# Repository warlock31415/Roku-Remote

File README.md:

# Roku Remote

## Introduction
My roomate keeps loosing the remote to the TV. So I made a spare remote to work with our TV and simulates the same behaviour as the original remote. The remote can also work via micro USB as well as a Lithium polymer battery. This project was my first forray into ARM microcontrollers and ST's Hardware Abstraction Layer (HAL).  

## Recording button codes
The Roku remote work on a IR signal and the data is modulated on the 37 kHz signal. The NEC protocol decription can be found [here](https://techdocs.altium.com/display/FPGA/NEC+Infrared+Transmission+Protocol) . A Analog Discovery along with the TSOP382 (IR receiver) was used to record the signal. The receiver demodulates the signal internally and only ouputs the data bits. Each button was pressed and the corresponding code was recorded. It was noted that each button had 2 codes associated with it. The first one was transmitted when the button was pressed and the second was transmitted when the button was held down. Only the last 4 bytes of the codes are shown here as the first 4 bytes are always the same (0x57E3).

The recorded button codes are as follows:
| Button | Code in HEX |  Last 4 bytes of the held down code|
|--------|-------------| ----------|
| Power  | 0x57E3E817 | 0x57E3E916 | 
| Back   | 0x57E36699 | 0x57E36798 |
| Home   | 0xCO3F | 0xC13E |
| ↑      | 0x9867 | 0x9966 |
| →      | 0xB44B | 0xB54A |
| ↓      | 0xCC33 | 0xCD32 |
| ←      | 0x7887 | 0x7986 |
| OK     | 0x54AB | 0x55AA |
| V+     | 0xF00F | 0xF10E |
| V-     | 0x08F7 | 0x09F6 |
| Mute   | 0x04FB | 0x05FA |

## The code
ST's Nucleo-F401RE(497-14360-ND) was used to build the remote on a breadboard. Although, a STM32L052K8T was actually used in the final prototype due to its lower power consumption as compared to the STM32F401RE.

The HAL does not have a microsecond delay so a timer was used. The following code shows how this works:
```
void delay_us(uint16_t time)
{
	TIM6->ARR = time; 	 	// Load time into Auto Reload Register
	TIM6->CR1 |= (1<<0); 	// start timer

	while(TIM6->CR1 & 1);	// Wait for timer to elapse
}
```
ST's Cube IDE makes it very easy to set up and use timers graphically. To generate the carrier another 16-bit advanced timer was used in PWM mode. The STM32F401RE has 16-bit prescale register which allows just about any frequency. This, combined with the Auto-Preload Register, one can generate just about any frequency signal with any duty cycle. So a 37kHz carrier with a 30% duty cycle, for efficiency, was generated. This Prescale and AR registers are especially more advatageous to an ATMEGA328P which only has a couple of prescalers to choose from and the "auto reload register" is the only way to control frequency. And hence duty cycle cannot be controlled in the same way.

Each button code consists of 3 sections. The start code, specific button code and the end code. This can be seen in Table 1.
## PCB
The PCB was made in Eagle and manufactured by JLCPCB. All components were hand soldered. Including, the STM32L052K8T. The blue silk screen on the PCBs look pretty good. 

## Shortcomings
- The SMD IR transmitter that was spec'd for the project didn't seem to work properly. So a THT transmitter, was was used to test the breadboard prototype, was soldered in its place. Some wire bodging was needed to accomplish this.
- The battery protection circuitry was not correctly wired up (Some kind of issue with Battery GND vs system GND).

## TO DO
- Redo board to eliminate wire bodges.
- Make a case for the board.

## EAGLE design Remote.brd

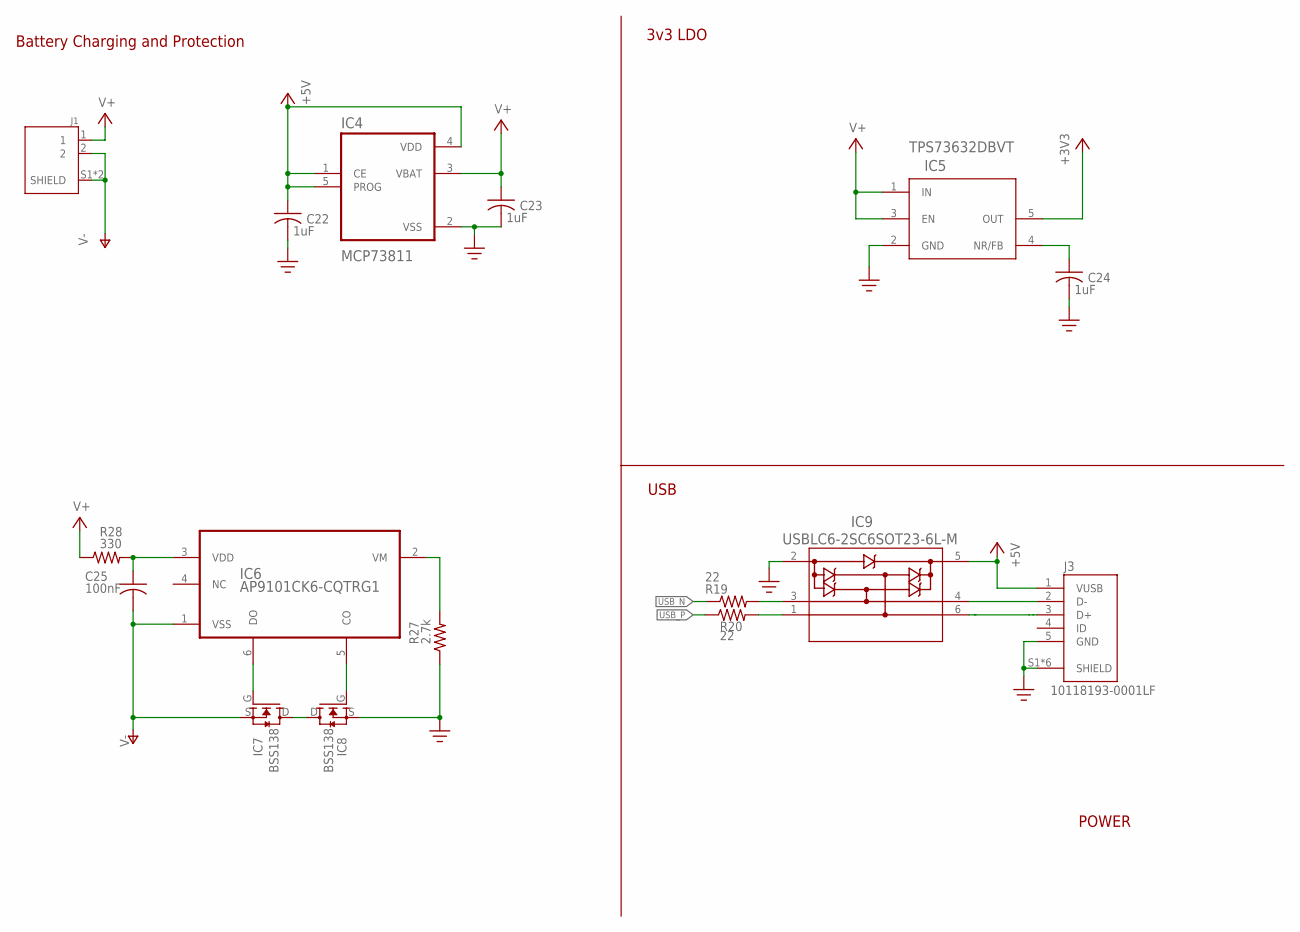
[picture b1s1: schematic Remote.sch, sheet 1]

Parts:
C22, C23, C24: 1uF; C0805K
C25: 100nF; C0805K
IC4: MCP73811; SOT95P280X145-5N
IC5: TPS73632DBVT; DBV5-M
IC6: AP9101CK6-CQTRG1; SOT95P280X140-6N
IC7, IC8: BSS138
IC9: USBLC6-2SC6SOT23-6L-M; SOT23-6L-M
J1: S2B-PH-SM4-TB(LF)(SN); JST_S2B-PH-SM4-TB(LF)(SN)
J3: 10118193-0001LF; FCI_10118193-0001LF
R19, R20: 22; R0805W
R27: 2.7k; R0805W
R28: 330; R0805W

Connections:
+3V3: IC5.5 (OUT); also elsewhere on the board
+5V: C22.1, IC4.1 (CE), IC4.4 (VDD), IC4.5 (PROG), IC9.5 (VBUS), J3.1 (VUSB); also elsewhere on the board
GND: C22.2, C23.2, C24.2, IC4.2 (VSS), IC5.2 (GND), IC8.S, IC9.2 (GND), J3.5 (GND), J3.S1 (SHIELD), J3.S2 (SHIELD), J3.S3 (SHIELD), J3.S4 (SHIELD), J3.S5 (SHIELD), J3.S6 (SHIELD), R27.1; also elsewhere on the board
unnamed: IC6.6 (DO), IC7.G
unnamed: IC6.5 (CO), IC8.G
unnamed: IC7.D, IC8.D
unnamed: C24.1, IC5.4 (NR/FB)
unnamed: IC6.2 (VM), R27.2
unnamed: C25.1, IC6.3 (VDD), R28.2
USB2_N: IC9.4 (I/O2), J3.2 (D-)
USB2_P: IC9.6 (I/O1), J3.3 (D+)
USB3_N: IC9.3 (I/O2_2), R19.2
USB3_P: IC9.1 (I/O1_2), R20.2
USB_N: R19.1; also elsewhere on the board
USB_P: R20.1; also elsewhere on the board
V+: C23.1, IC4.3 (VBAT), IC5.1 (IN), IC5.3 (EN), J1.1, R28.1; also elsewhere on the board
V-: C25.2, IC6.1 (VSS), IC7.S, J1.2, J1.S1 (SHIELD), J1.S2 (SHIELD)

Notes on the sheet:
Battery Charging and Protection
3v3 LDO
USB
POWER

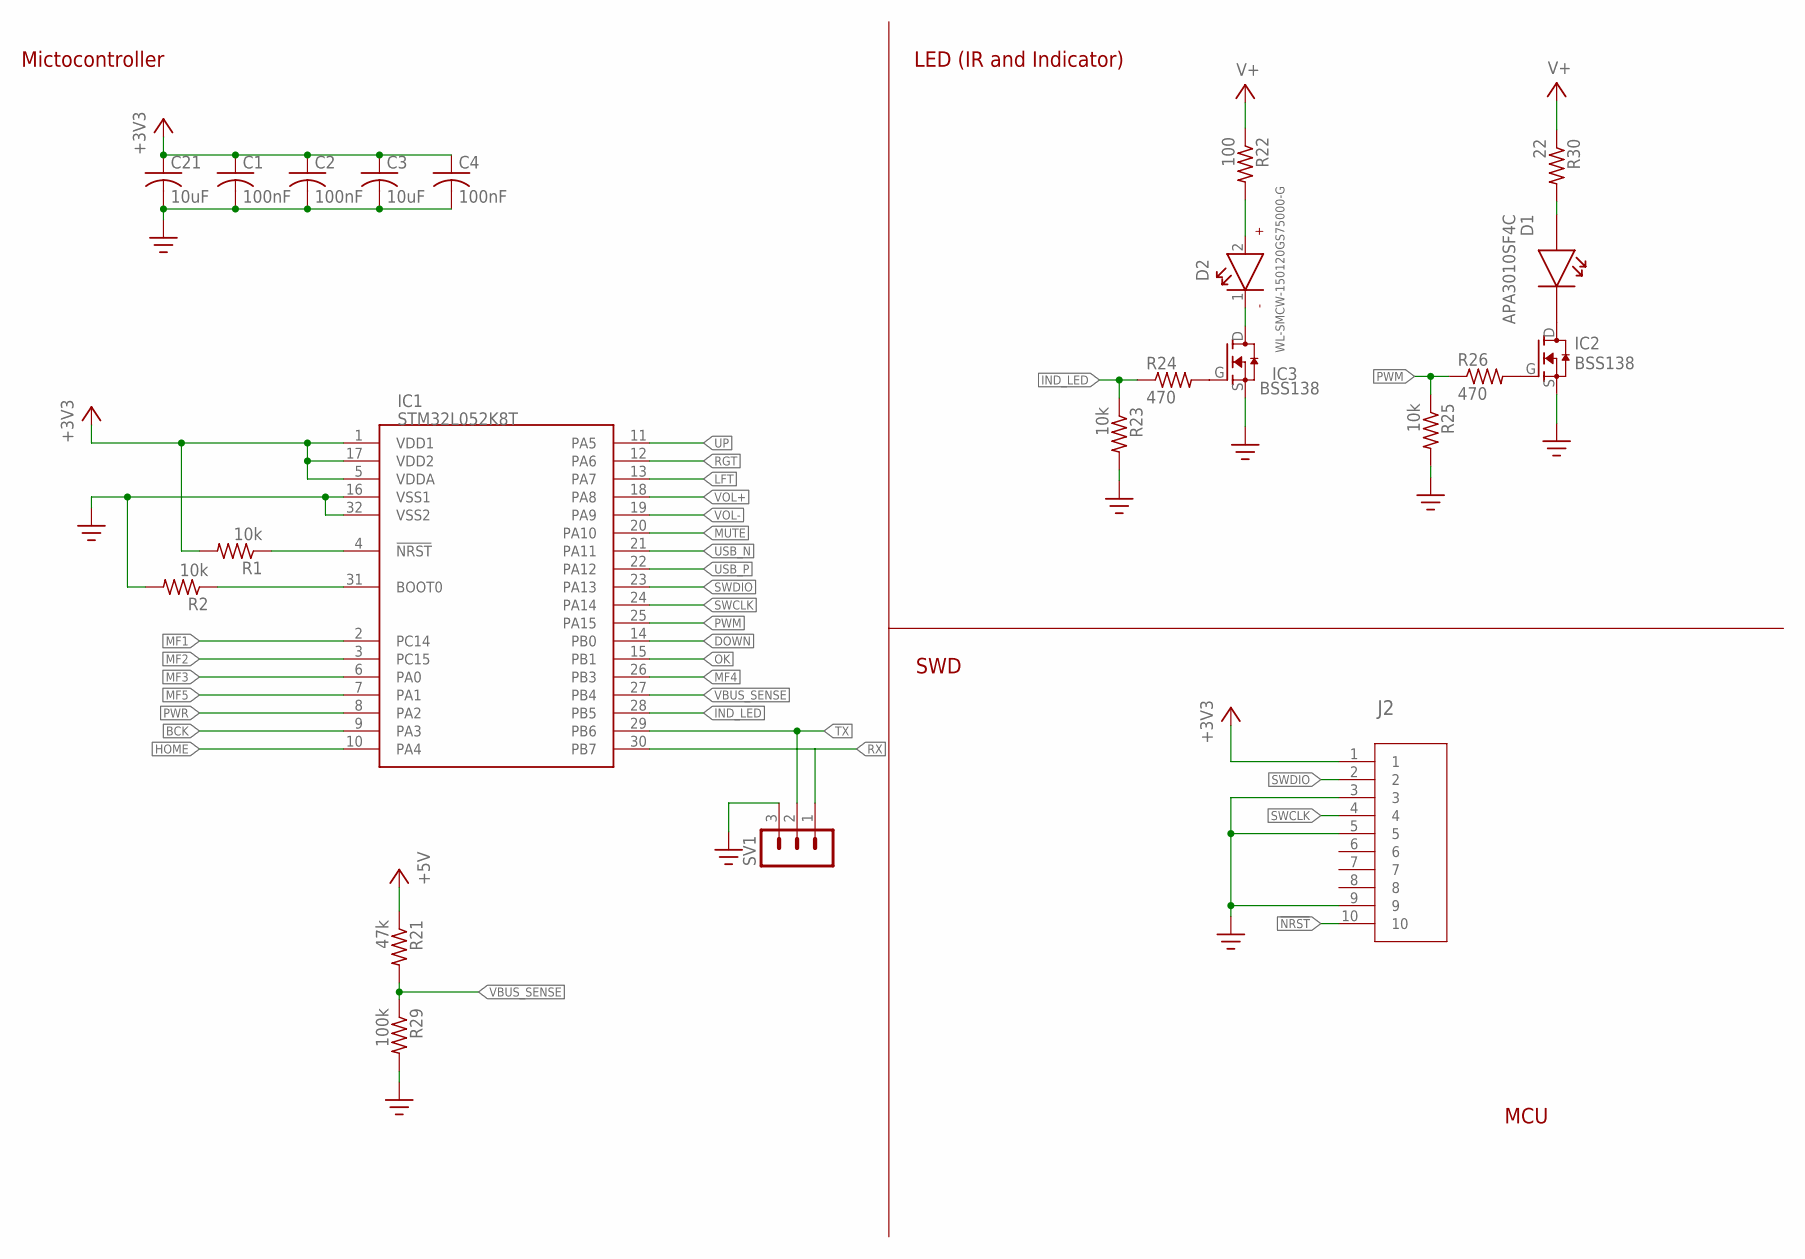
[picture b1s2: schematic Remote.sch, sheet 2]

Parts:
C1, C2, C4: 100nF; C0805K
C3, C21: 10uF; C0805K
D1: APA3010SF4C
D2: WL-SMCW-150120GS75000-G; WL-SMCW_1206
IC1: STM32L052K8T; QFP80P900X900X160-32N
IC2, IC3: BSS138
J2: 20021121-00010C4LF; CONN_00010C4LF_AMP
R1, R2, R23, R25: 10k; R0805W
R21: 47k; R0805W
R22: 100; R0805W
R24, R26: 470; R0805W
R29: 100k; R0805W
R30: 22; R0805W
SV1: MA03-1

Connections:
!NRST: IC1.4 (!NRST), J2.10, R1.1
+3V3: C1.1, C2.1, C3.1, C4.1, C21.1, IC1.1 (VDD1), IC1.5 (VDDA), IC1.17 (VDD2), J2.1, R1.2; also elsewhere on the board
+5V: R21.1; also elsewhere on the board
BCK: IC1.9 (PA3); also elsewhere on the board
DOWN: IC1.14 (PB0); also elsewhere on the board
GND: C1.2, C2.2, C3.2, C4.2, C21.2, IC1.16 (VSS1), IC1.32 (VSS2), IC2.S, IC3.S, J2.3, J2.5, J2.9, R2.2, R23.2, R25.2, R29.2, SV1.3; also elsewhere on the board
HOME: IC1.10 (PA4); also elsewhere on the board
IND_LED: IC1.28 (PB5), R23.1, R24.1
LFT: IC1.13 (PA7); also elsewhere on the board
MF1: IC1.2 (PC14); also elsewhere on the board
MF2: IC1.3 (PC15); also elsewhere on the board
MF3: IC1.6 (PA0); also elsewhere on the board
MF4: IC1.26 (PB3); also elsewhere on the board
MF5: IC1.7 (PA1); also elsewhere on the board
MUTE: IC1.20 (PA10); also elsewhere on the board
unnamed: D1.1, R30.2
unnamed: IC1.31 (BOOT0), R2.1
unnamed: D1.2, IC2.D
unnamed: D2.2 (+), R22.2
unnamed: D2.1 (-), IC3.D
unnamed: IC2.G, R26.2
unnamed: IC3.G, R24.2
OK: IC1.15 (PB1); also elsewhere on the board
PWM: IC1.25 (PA15), R25.1, R26.1
PWR: IC1.8 (PA2); also elsewhere on the board
RGT: IC1.12 (PA6); also elsewhere on the board
RX: IC1.30 (PB7), SV1.1
SWCLK: IC1.24 (PA14), J2.4
SWDIO: IC1.23 (PA13), J2.2
TX: IC1.29 (PB6), SV1.2
UP: IC1.11 (PA5); also elsewhere on the board
USB_N: IC1.21 (PA11); also elsewhere on the board
USB_P: IC1.22 (PA12); also elsewhere on the board
V+: R22.1, R30.1; also elsewhere on the board
VBUS_SENSE: IC1.27 (PB4), R21.2, R29.1
VOL+: IC1.18 (PA8); also elsewhere on the board
VOL-: IC1.19 (PA9); also elsewhere on the board

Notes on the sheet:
Mictocontroller
LED (IR and Indicator)
SWD
MCU

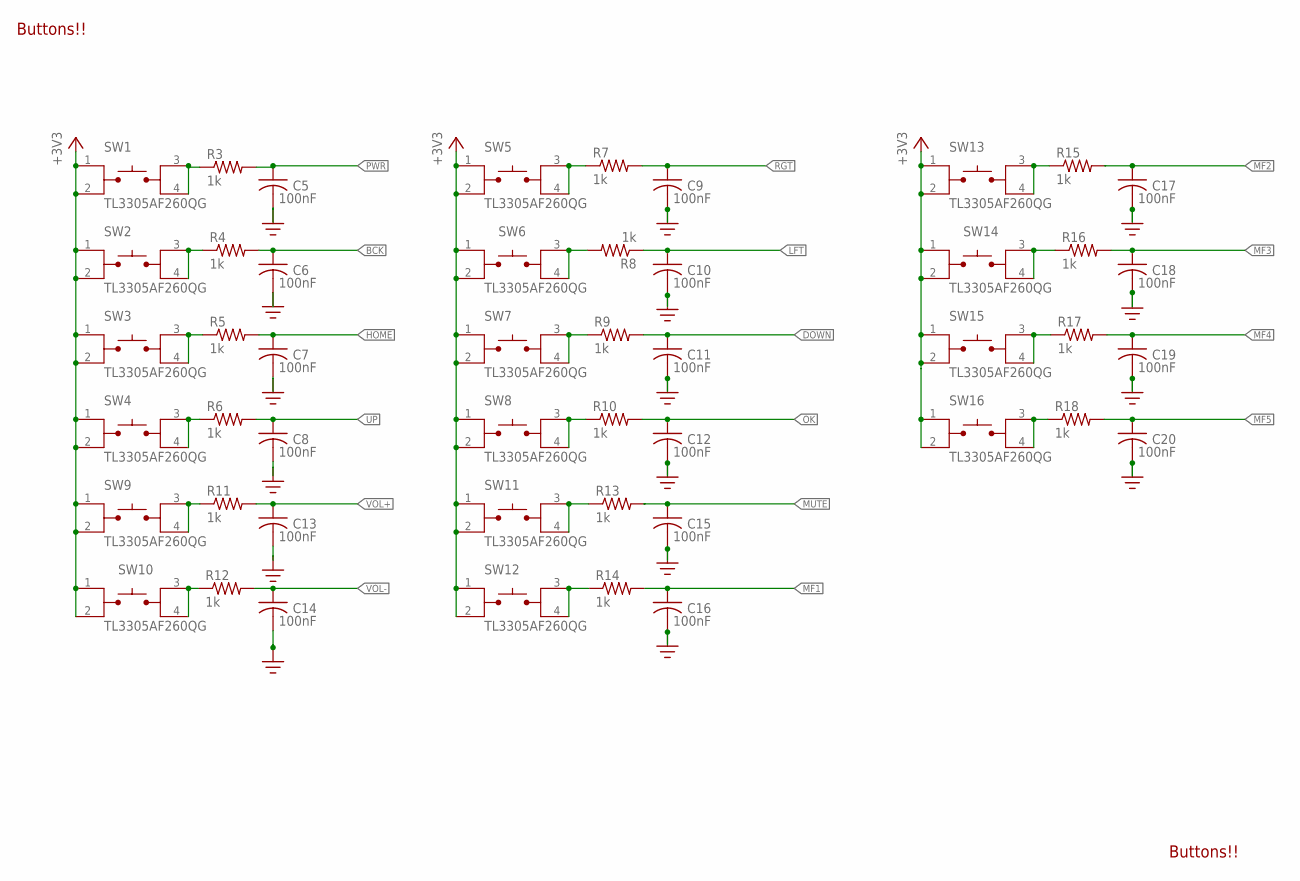
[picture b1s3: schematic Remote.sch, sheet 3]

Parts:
C5, C6, C7, C8, C9, C10, C11, C12, C13, C14, C15, C16, C17, C18, C19, C20: 100nF; C0805K
R3, R4, R5, R6, R7, R8, R9, R10, R11, R12, R13, R14, R15, R16, R17, R18: 1k; R0805W
SW1, SW2, SW3, SW4, SW5, SW6, SW7, SW8, SW9, SW10, SW11, SW12, SW13, SW14, SW15, SW16: TL3305AF260QG; SW_TL3305AF260QG

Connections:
+3V3: SW1.1, SW1.2, SW2.1, SW2.2, SW3.1, SW3.2, SW4.1, SW4.2, SW5.1, SW5.2, SW6.1, SW6.2, SW7.1, SW7.2, SW8.1, SW8.2, SW9.1, SW9.2, SW10.1, SW10.2, SW11.1, SW11.2, SW12.1, SW12.2, SW13.1, SW13.2, SW14.1, SW14.2, SW15.1, SW15.2, SW16.1, SW16.2; also elsewhere on the board
BCK: C6.1, R4.2; also elsewhere on the board
DOWN: C11.1, R9.2; also elsewhere on the board
GND: C5.2, C6.2, C7.2, C8.2, C9.2, C10.2, C11.2, C12.2, C13.2, C14.2, C15.2, C16.2, C17.2, C18.2, C19.2, C20.2; also elsewhere on the board
HOME: C7.1, R5.2; also elsewhere on the board
LFT: C10.1, R8.1; also elsewhere on the board
MF1: C16.1, R14.2; also elsewhere on the board
MF2: C17.1, R15.2; also elsewhere on the board
MF3: C18.1, R16.2; also elsewhere on the board
MF4: C19.1, R17.2; also elsewhere on the board
MF5: C20.1, R18.2; also elsewhere on the board
MUTE: C15.1, R13.2; also elsewhere on the board
unnamed: R3.1, SW1.3, SW1.4
unnamed: R4.1, SW2.3, SW2.4
unnamed: R5.1, SW3.3, SW3.4
unnamed: R6.1, SW4.3, SW4.4
unnamed: R11.1, SW9.3, SW9.4
unnamed: R12.1, SW10.3, SW10.4
unnamed: R7.1, SW5.3, SW5.4
unnamed: R8.2, SW6.3, SW6.4
unnamed: R9.1, SW7.3, SW7.4
unnamed: R10.1, SW8.3, SW8.4
unnamed: R13.1, SW11.3, SW11.4
unnamed: R14.1, SW12.3, SW12.4
unnamed: R15.1, SW13.3, SW13.4
unnamed: R16.1, SW14.3, SW14.4
unnamed: R17.1, SW15.3, SW15.4
unnamed: R18.1, SW16.3, SW16.4
OK: C12.1, R10.2; also elsewhere on the board
PWR: C5.1, R3.2; also elsewhere on the board
RGT: C9.1, R7.2; also elsewhere on the board
UP: C8.1, R6.2; also elsewhere on the board
VOL+: C13.1, R11.2; also elsewhere on the board
VOL-: C14.1, R12.2; also elsewhere on the board

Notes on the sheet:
Buttons!!

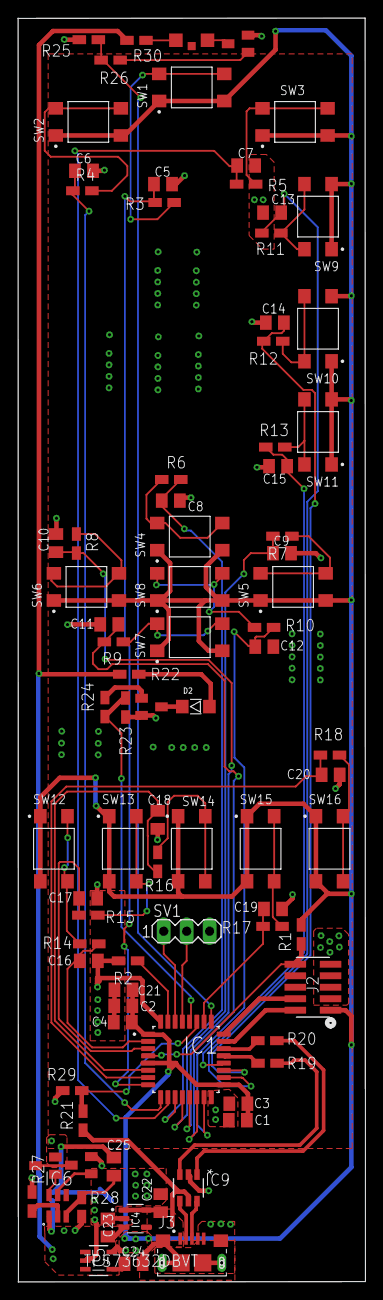
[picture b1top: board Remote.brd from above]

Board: 2 copper layers, 38.4 x 139.8 mm, 86 parts (1 on the bottom side), 64 nets.

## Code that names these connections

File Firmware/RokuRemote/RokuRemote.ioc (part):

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Mcu.Name=STM32L052K(6-8)Tx
Mcu.Package=LQFP32
Mcu.UserName=STM32L052K8Tx
PA0.GPIOParameters=GPIO_PuPd,GPIO_Label
PA0.GPIO_Label=MF3
PA0.GPIO_PuPd=GPIO_PULLDOWN
PA0.Signal=GPIO_Input
PA1.GPIOParameters=GPIO_PuPd,GPIO_Label
PA1.GPIO_Label=MF5
PA1.GPIO_PuPd=GPIO_PULLDOWN
PA1.Signal=GPIO_Input
PA10.GPIOParameters=GPIO_PuPd,GPIO_Label
PA10.GPIO_Label=MUTE
PA10.GPIO_PuPd=GPIO_PULLDOWN
PA10.Signal=GPXTI10
PA11.Mode=Device
PA11.Signal=USB_DM
PA12.Mode=Device
PA12.Signal=USB_DP
PA13.Mode=Serial_Wire
PA13.Signal=SYS_SWDIO
PA14.Mode=Serial_Wire
PA14.Signal=SYS_SWCLK
PA15.GPIOParameters=GPIO_Label
PA15.GPIO_Label=PWM
PA15.Signal=S_TIM2_CH1
PA2.GPIOParameters=GPIO_PuPd,GPIO_Label,GPIO_ModeDefaultEXTI
PA2.GPIO_Label=PWR
PA2.GPIO_ModeDefaultEXTI=GPIO_MODE_IT_RISING
PA2.GPIO_PuPd=GPIO_PULLDOWN
PA2.Signal=GPXTI2
PA3.GPIOParameters=GPIO_PuPd,GPIO_Label
PA3.GPIO_Label=BCK
PA3.GPIO_PuPd=GPIO_PULLDOWN
PA3.Signal=GPXTI3
PA4.GPIOParameters=GPIO_PuPd,GPIO_Label
PA4.GPIO_Label=HOME
PA4.GPIO_PuPd=GPIO_PULLDOWN
PA4.Signal=GPXTI4
PA5.GPIOParameters=GPIO_PuPd,GPIO_Label
PA5.GPIO_Label=UP
PA5.GPIO_PuPd=GPIO_PULLDOWN
PA5.Signal=GPXTI5
PA6.GPIOParameters=GPIO_PuPd,GPIO_Label
PA6.GPIO_Label=RGT
PA6.GPIO_PuPd=GPIO_PULLDOWN
PA6.Signal=GPXTI6
PA7.GPIOParameters=GPIO_PuPd,GPIO_Label
PA7.GPIO_Label=LFT
PA7.GPIO_PuPd=GPIO_PULLDOWN
PA7.Signal=GPXTI7
PA8.GPIOParameters=GPIO_PuPd,GPIO_Label
PA8.GPIO_Label=V+
PA8.GPIO_PuPd=GPIO_PULLDOWN
PA8.Signal=GPXTI8
PA9.GPIOParameters=GPIO_PuPd,GPIO_Label
PA9.GPIO_Label=V-
PA9.GPIO_PuPd=GPIO_PULLDOWN
PA9.Signal=GPXTI9
PB0.GPIOParameters=GPIO_PuPd,GPIO_Label
PB0.GPIO_Label=DWN
PB0.GPIO_PuPd=GPIO_PULLDOWN
PB0.Signal=GPXTI0
PB1.GPIOParameters=GPIO_PuPd,GPIO_Label
PB1.GPIO_Label=OK
PB1.GPIO_PuPd=GPIO_PULLDOWN
PB1.Signal=GPXTI1
PB3.GPIOParameters=GPIO_PuPd,GPIO_Label
PB3.GPIO_Label=MF4
PB3.GPIO_PuPd=GPIO_PULLDOWN
PB3.Signal=GPIO_Input
PB4.GPIOParameters=GPIO_PuPd,GPIO_Label
PB4.GPIO_Label=USB_SENSE
PB4.GPIO_PuPd=GPIO_PULLDOWN
PB4.Signal=GPIO_Input
PB5.GPIOParameters=GPIO_PuPd,GPIO_Label
PB5.GPIO_Label=LED_IND
PB5.GPIO_PuPd=GPIO_PULLDOWN
PB5.Signal=GPIO_Output
PB6.Mode=Asynchronous
PB6.Signal=USART1_TX
PB7.Mode=Asynchronous
PB7.Signal=USART1_RX
PC14-OSC32_IN.GPIOParameters=GPIO_PuPd,GPIO_Label
PC14-OSC32_IN.GPIO_Label=MF1
PC14-OSC32_IN.GPIO_PuPd=GPIO_PULLDOWN
PC14-OSC32_IN.Signal=GPIO_Input
PC15-OSC32_OUT.GPIOParameters=GPIO_PuPd,GPIO_Label
PC15-OSC32_OUT.GPIO_Label=MF2
PC15-OSC32_OUT.GPIO_PuPd=GPIO_PULLDOWN
PC15-OSC32_OUT.Signal=GPIO_Input
RCC.SYSCLKFreq_VALUE=24000000
RCC.SYSCLKSource=RCC_SYSCLKSOURCE_PLLCLK
board=custom

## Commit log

2020-09-15 Set theme jekyll-theme-cayman
2020-09-22 Made separate folders for Hardware and firmware moved appropriate files
2020-09-22 Added a image of the PCB
2021-01-12 Spell check

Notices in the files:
parts and their libraries:
Remote: COPYRIGHT: Copyright (C) 2018 Accelerated Designs. All rights reserved
